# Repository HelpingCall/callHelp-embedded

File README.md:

# callHelp-embedded

CallForHelp Embedded Project

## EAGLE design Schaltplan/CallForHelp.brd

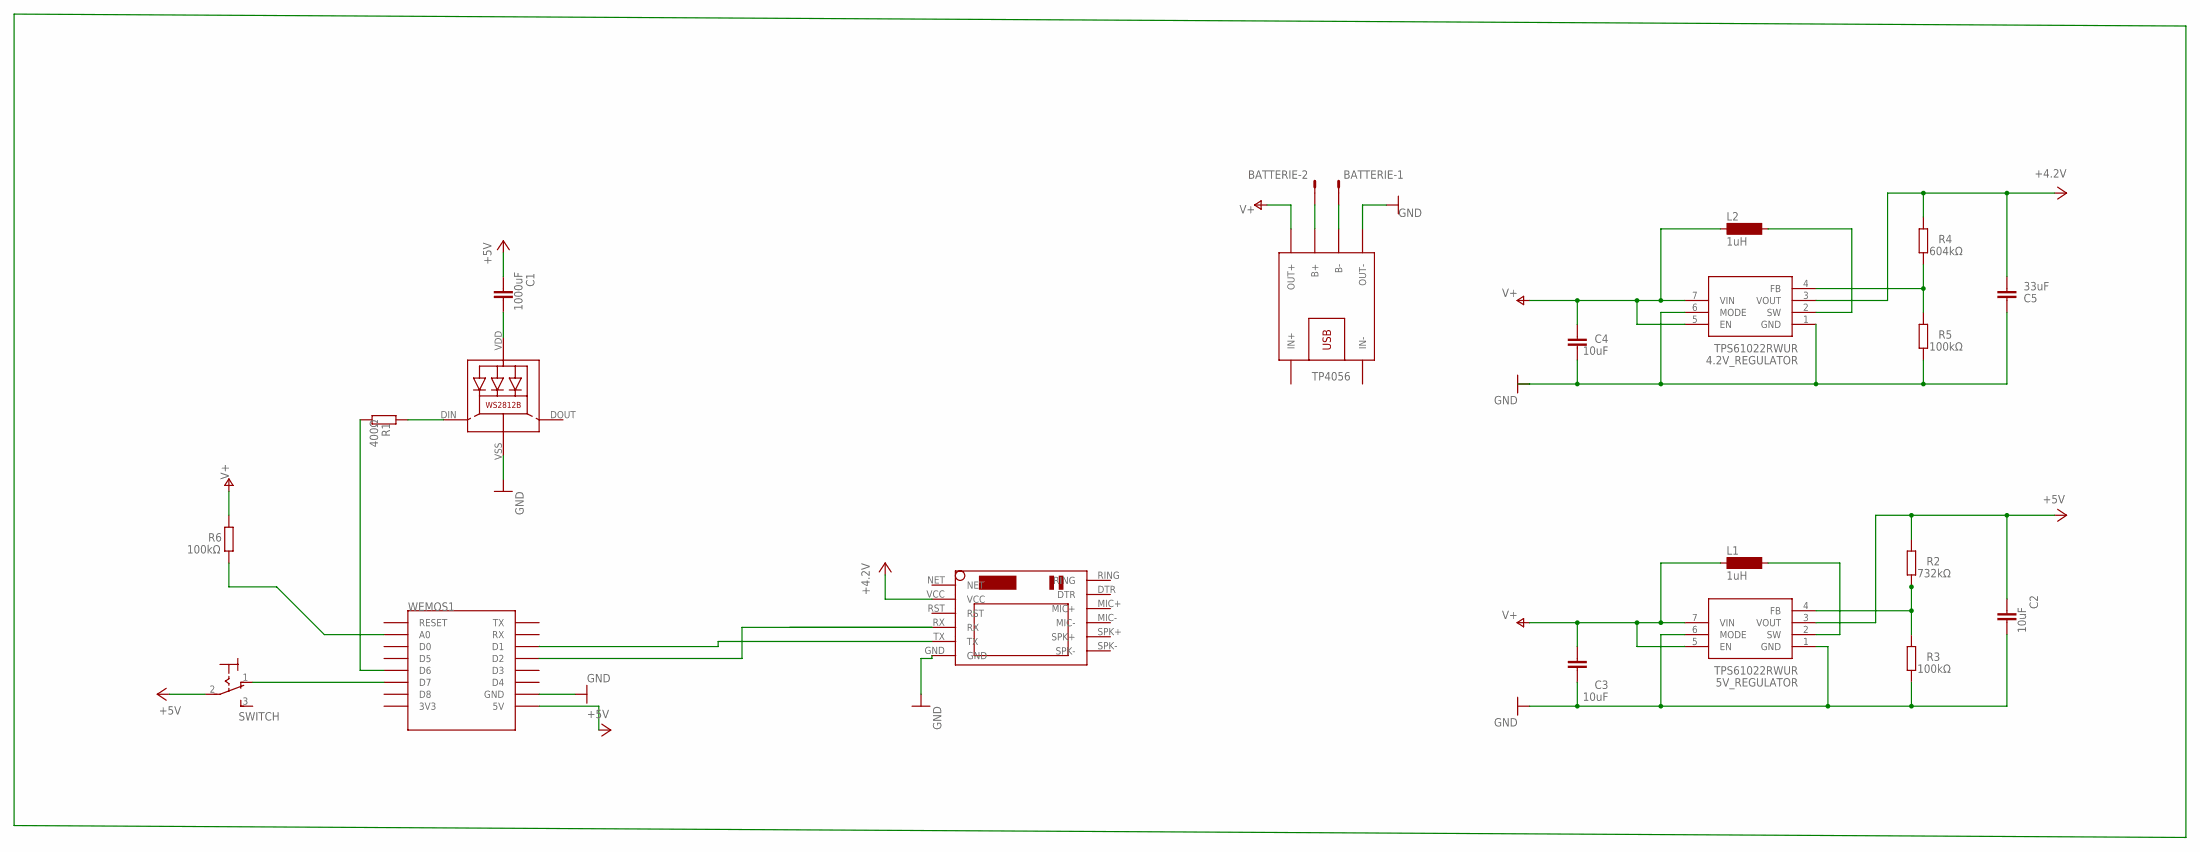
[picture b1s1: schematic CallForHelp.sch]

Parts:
4.2V_REGULATOR, 5V_REGULATOR: TPS61022RWUR
BATTERIE: L02P
C1: 1000uF; C2.5-3
C2, C3, C4: 10uF; C2.5-3
C5: 33uF; C2.5-3
L1, L2: 1uH; SM-L15A
LED1: WS2812B
R1: 400Ω; 0204/7
R2: 732kΩ; 0204/7
R3, R5, R6: 100kΩ; 0204/7
R4: 604kΩ; 0204/7
SIM800L: SIM800LMODULE
SWITCH: 320-916
TP4056: BATTERY-CHARGER-LI-PROT
WEMOS1: WEMOS-D1-MINI

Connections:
+5V: 5V_REGULATOR.3 (VOUT), C1.1, C2.1, R2.2, SWITCH.2, WEMOS1.5V
BATTERY_GND: BATTERIE.1, TP4056.B-
BATTERY_VCC: BATTERIE.2, TP4056.B+
GND: 4.2V_REGULATOR.1 (GND), 4.2V_REGULATOR.6 (MODE), 5V_REGULATOR.1 (GND), 5V_REGULATOR.6 (MODE), C2.2, C3.2, C4.2, C5.1, LED1.VSS (GND), R3.1, R5.1, SIM800L.GND, TP4056.OUT-, WEMOS1.GND
LED_PIN: R1.1, WEMOS1.D6
unnamed: 5V_REGULATOR.4 (FB), R2.1, R3.2
unnamed: LED1.DIN (DI), R1.2
unnamed: 4.2V_REGULATOR.4 (FB), R4.1, R5.2
unnamed: R6.1, WEMOS1.A0
unnamed: SIM800L.RX, WEMOS1.D2
unnamed: SIM800L.TX, WEMOS1.D1
unnamed: SWITCH.1 (O), WEMOS1.D7
unnamed: 4.2V_REGULATOR.2 (SW), L2.2
unnamed: 5V_REGULATOR.2 (SW), L1.2
unnamed: C1.2, LED1.VDD
V+: 4.2V_REGULATOR.5 (EN), 4.2V_REGULATOR.7 (VIN), 5V_REGULATOR.5 (EN), 5V_REGULATOR.7 (VIN), C3.1, C4.1, L1.1, L2.1, R6.2, TP4056.OUT+
VCC: 4.2V_REGULATOR.3 (VOUT), C5.2, R4.2, SIM800L.VCC

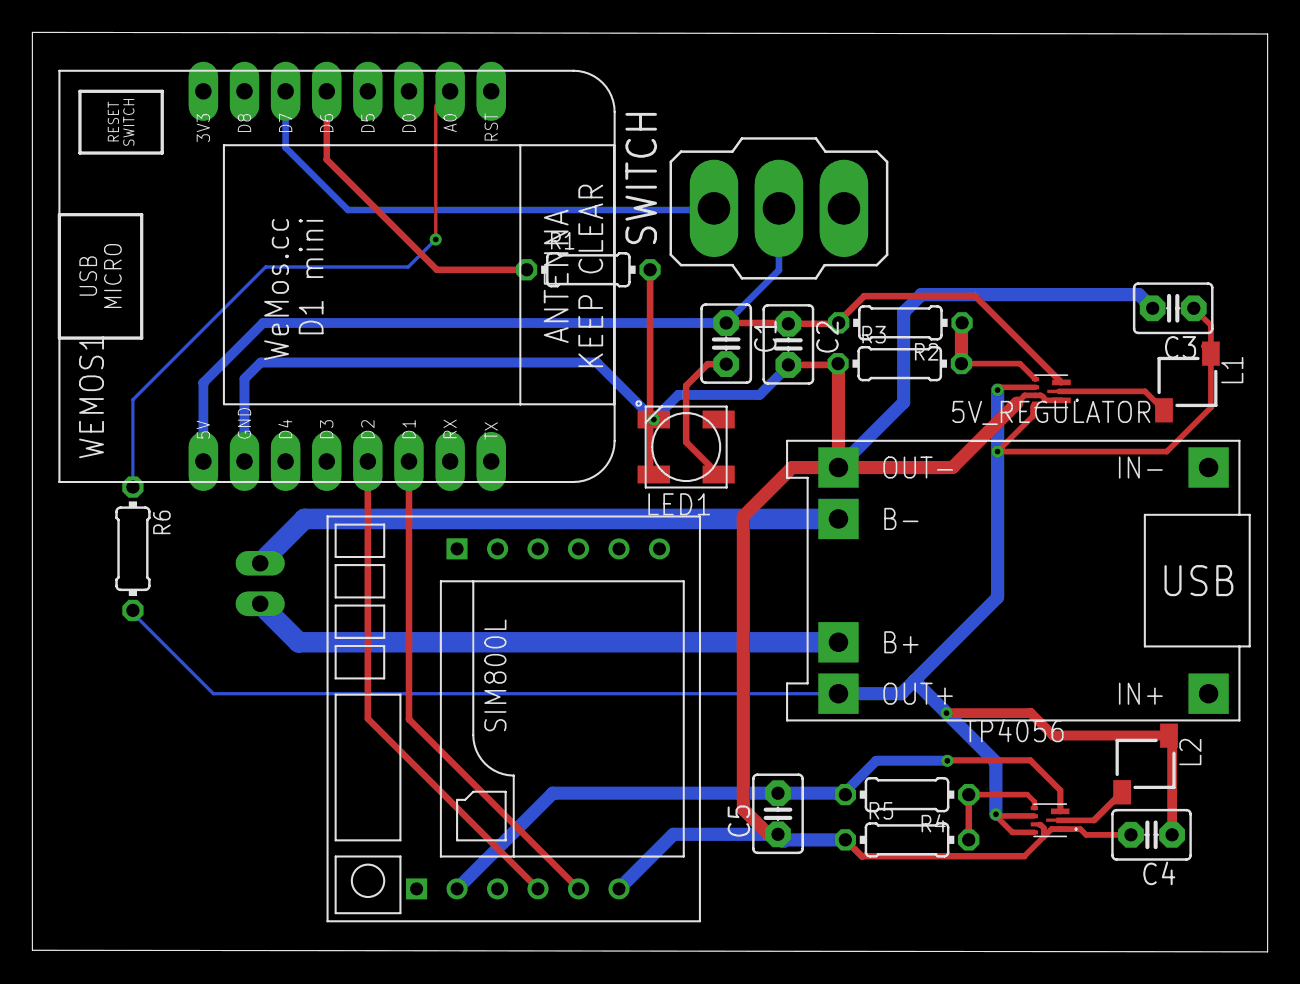
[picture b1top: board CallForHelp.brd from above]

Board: 2 copper layers, 76.3 x 56.8 mm, 21 parts (1 on the bottom side), 17 nets.

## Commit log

2020-09-18 Renewed schaltplan
2020-09-18 Renewd board
2020-09-18 updated versions

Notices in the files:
parts and their libraries:
TP4056 - Lipo Charger: Released under the Creative Commons Attribution 4.0 International License: http://creativecommons.org/licenses/by/4.0
